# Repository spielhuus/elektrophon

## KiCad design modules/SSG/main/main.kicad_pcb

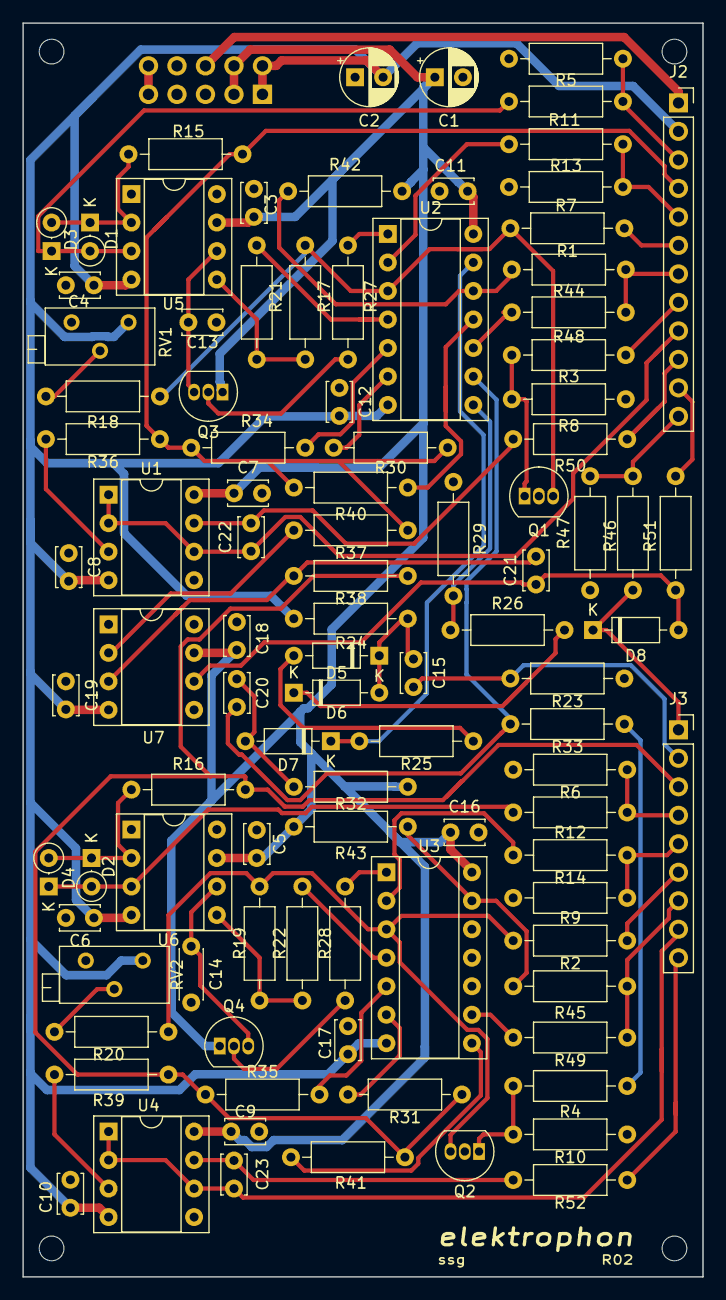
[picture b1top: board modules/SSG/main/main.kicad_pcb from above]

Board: 2 copper layers, 60.6 x 111.8 mm, 99 parts (1 on the bottom side), 70 nets.

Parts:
C1, C2: 10u; CP_Radial_D5.0mm_P2.50mm
C3, C4, C5, C6, C7, C8, C9, C10, C11, C12, C16, C17, C18, C19: 0.1u; C_Disc_D3.4mm_W2.1mm_P2.50mm
C13: 100n; C_Disc_D3.4mm_W2.1mm_P2.50mm
C14: 220n; C_Disc_D4.3mm_W1.9mm_P5.00mm
C15, C20: 1n; C_Disc_D3.4mm_W2.1mm_P2.50mm
C21: 100p; C_Disc_D3.4mm_W2.1mm_P2.50mm
C22, C23: 47p; C_Disc_D3.4mm_W2.1mm_P2.50mm
D1, D2, D3, D4: 1N4148; D_DO-35_SOD27_P2.54mm_Vertical_KathodeUp
D5, D6, D7, D8: 1N4148; D_DO-35_SOD27_P7.62mm_Horizontal
J1: IDC Header; IDC-Header_2x05_P2.54mm_Vertical
J2: Conn_01x12_Female; PinSocket_1x12_P2.54mm_Vertical
J3: Conn_01x09_Female; PinSocket_1x09_P2.54mm_Vertical
Q1, Q2: PN4250; TO-92_Inline
Q3, Q4: J201; TO-92_Inline
R1, R2, R13, R14: 2M7; R_Axial_DIN0207_L6.3mm_D2.5mm_P10.16mm_Horizontal
R3, R4, R5, R6, R11, R12, R15, R16, R24: 33k; R_Axial_DIN0207_L6.3mm_D2.5mm_P10.16mm_Horizontal
R7, R9, R23, R26: 100k; R_Axial_DIN0207_L6.3mm_D2.5mm_P10.16mm_Horizontal
R8, R10, R21, R22: 15k; R_Axial_DIN0207_L6.3mm_D2.5mm_P10.16mm_Horizontal
R17, R19: 82k; R_Axial_DIN0207_L6.3mm_D2.5mm_P10.16mm_Horizontal
R18, R20, R32: 1M5; R_Axial_DIN0207_L6.3mm_D2.5mm_P10.16mm_Horizontal
R25: 680k; R_Axial_DIN0207_L6.3mm_D2.5mm_P10.16mm_Horizontal
R27, R31: 820k; R_Axial_DIN0207_L6.3mm_D2.5mm_P10.16mm_Horizontal
R28: 1m; R_Axial_DIN0207_L6.3mm_D2.5mm_P10.16mm_Horizontal
R29: 4M7; R_Axial_DIN0207_L6.3mm_D2.5mm_P10.16mm_Horizontal
R30, R42, R43: 1M; R_Axial_DIN0207_L6.3mm_D2.5mm_P10.16mm_Horizontal
R33, R34, R35: 330; R_Axial_DIN0207_L6.3mm_D2.5mm_P10.16mm_Horizontal
R36, R37, R38, R39: 10k; R_Axial_DIN0207_L6.3mm_D2.5mm_P10.16mm_Horizontal
R40, R41: 470k; R_Axial_DIN0207_L6.3mm_D2.5mm_P10.16mm_Horizontal
R44, R45: 2M2; R_Axial_DIN0207_L6.3mm_D2.5mm_P10.16mm_Horizontal
R46, R47, R48, R49, R51: 3k3; R_Axial_DIN0207_L6.3mm_D2.5mm_P10.16mm_Horizontal
R50, R52: 100; R_Axial_DIN0207_L6.3mm_D2.5mm_P10.16mm_Horizontal
RV1, RV2: 25k; Potentiometer_Bourns_3296Z_Horizontal
U1, U4: TL072; DIP-8_W7.62mm_Socket
U2, U3: LM3900; DIP-14_W7.62mm_Socket
U5, U6: CA3080; DIP-8_W7.62mm_Socket
U7: LM741; DIP-8_W7.62mm_Socket

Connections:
+5V: J1.9, J1.10
+15V: C1.1, C3.1, C5.1, C7.1, C9.1, C11.1, C16.1, C18.1, J1.3, J1.4, Q3.1, Q4.1, R32.2, R42.2, R43.2, U1.8, U2.14, U3.14, U4.8, U5.7, U6.7, U7.7
-15V: C2.2, C4.2, C6.2, C8.2, C10.2, C12.2, C17.2, C19.2, J1.1, J1.2, J2.2, R24.1, RV1.1, RV2.1, U1.4, U2.7, U3.7, U4.4, U5.4, U6.4, U7.4
/HOLD: R4.2, R33.1
COUPLER_5V: J2.12, R46.1, R47.2
COUPLER_HOT: J2.11, R51.1
CYCLE_1: J2.7, R44.1, R48.1
CYCLE_2: J3.7, R45.1, R49.1
GND: C1.2, C2.1, C3.2, C4.1, C5.2, C6.1, C7.2, C8.1, C9.2, C10.1, C11.2, C12.1, C13.2, C14.2, C16.2, C17.1, C18.2, C19.1, J1.5, J1.6, J1.7, J1.8, J2.1, Q1.2, Q2.2, R5.1, R6.1, R7.1, R8.1, R9.1, R10.1, R23.1, R29.1, R47.1, RV1.3, RV2.3, U1.5, U4.5
HOLD_1: J2.8, R3.2
IN_1: J2.3, R5.2, R11.2
IN_2: J3.4, R6.2, R12.2
LED: D8.1, J3.1, R46.2
LED_1_a: C22.1, J2.9, U1.1, U1.2, U1.6
LED_1_b: J2.10, R50.1
LED_2_a: C23.1, J3.8, U4.1, U4.2, U4.6
LED_2_b: J3.9, R52.1
unnamed: C13.1, Q3.3, U5.6
unnamed: C14.1, Q4.3, U6.6
unnamed: C15.2, D5.1, D6.2, R24.2
unnamed: C20.1, R33.2, U2.9
unnamed: C20.2, D7.2, R32.1
unnamed: C21.1, D8.2, R51.2, U7.6
unnamed: C21.2, R38.1, U7.3
unnamed: C22.2, R50.2, U1.7
unnamed: C23.2, R52.2, U4.7
unnamed: D1.1, D3.2, R15.2, U5.2
unnamed: D1.2, D3.1, R11.1, U5.3
unnamed: D2.1, D4.2, R16.2, U6.2
unnamed: D2.2, D4.1, R12.1, U6.3
unnamed: D5.2, R25.2
unnamed: D6.1, R26.2
unnamed: D7.1, R25.1, U2.13
unnamed: Q1.1, R3.1, R8.2
unnamed: Q1.3, R1.1, R17.2, R18.2, U2.3
unnamed: Q2.1, R4.1, R10.2
unnamed: Q2.3, R2.1, R19.2, R20.2, U3.3
unnamed: Q3.2, R27.2
unnamed: Q4.2, R28.2
unnamed: R13.1, U2.2
unnamed: R14.1, U3.2
unnamed: R17.1, R21.1, U5.5
unnamed: R18.1, RV1.2
unnamed: R19.1, R22.1, U6.5
unnamed: R20.1, RV2.2
unnamed: R21.2, U2.4
unnamed: R22.2, U3.4
unnamed: R26.1, R29.2, U2.8
unnamed: R27.1, U2.1
unnamed: R28.1, U3.1
unnamed: R30.1, U2.6
unnamed: R31.1, U3.6
unnamed: R34.2, U2.5
unnamed: R35.2, U3.5
unnamed: R36.1, U1.3
unnamed: R37.1, U7.2
unnamed: R39.1, U4.3
unnamed: R40.1, U2.11
unnamed: R41.1, U3.8
unnamed: R42.1, R44.2, U2.12
unnamed: R43.1, R45.2, U3.13
unnamed: R48.2, U2.10
unnamed: R49.2, U3.9
OUT_1: J2.4, R15.1, R30.2, R34.1, R36.2, R37.2, R40.2
OUT_2: J3.3, R16.1, R31.2, R35.1, R38.2, R39.2, R41.2
RATE_1: J2.6, R1.2
RATE_2: J3.6, R2.2
SAMPLE_2: C15.1, J3.2, R23.2
VC_1: J2.5, R7.2, R13.2
VC_2: J3.5, R9.2, R14.2

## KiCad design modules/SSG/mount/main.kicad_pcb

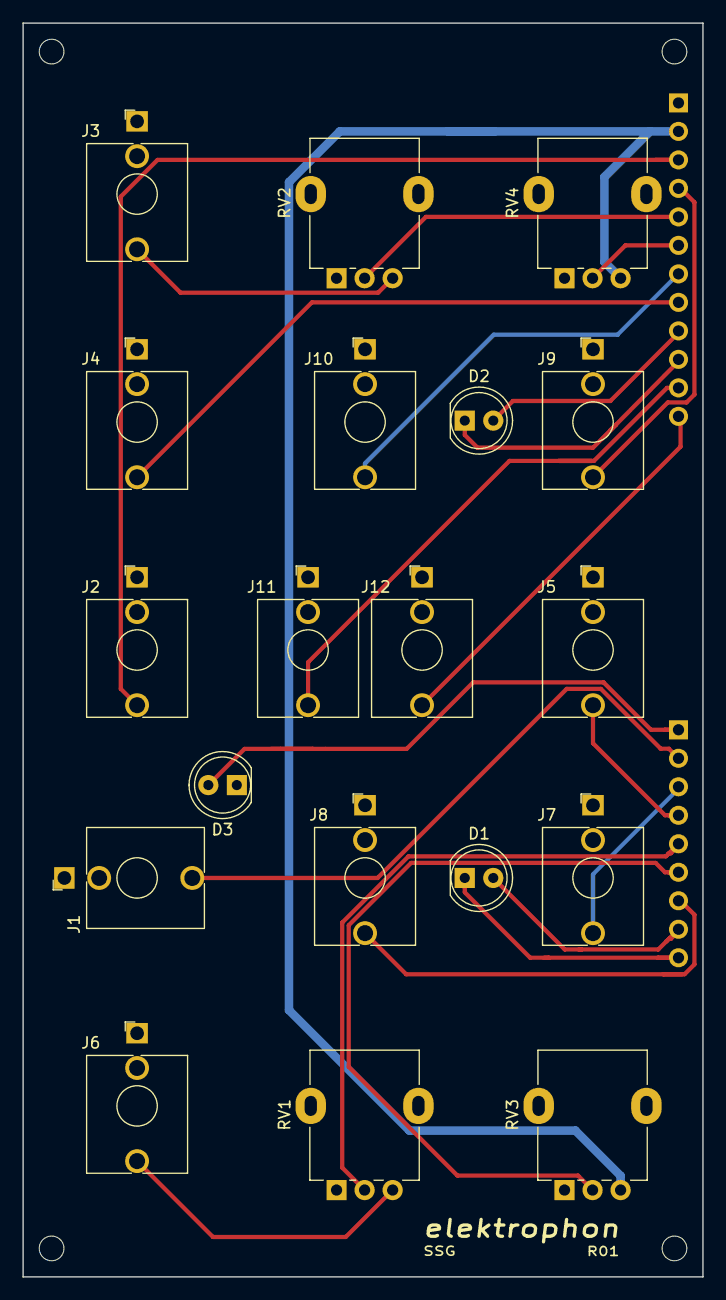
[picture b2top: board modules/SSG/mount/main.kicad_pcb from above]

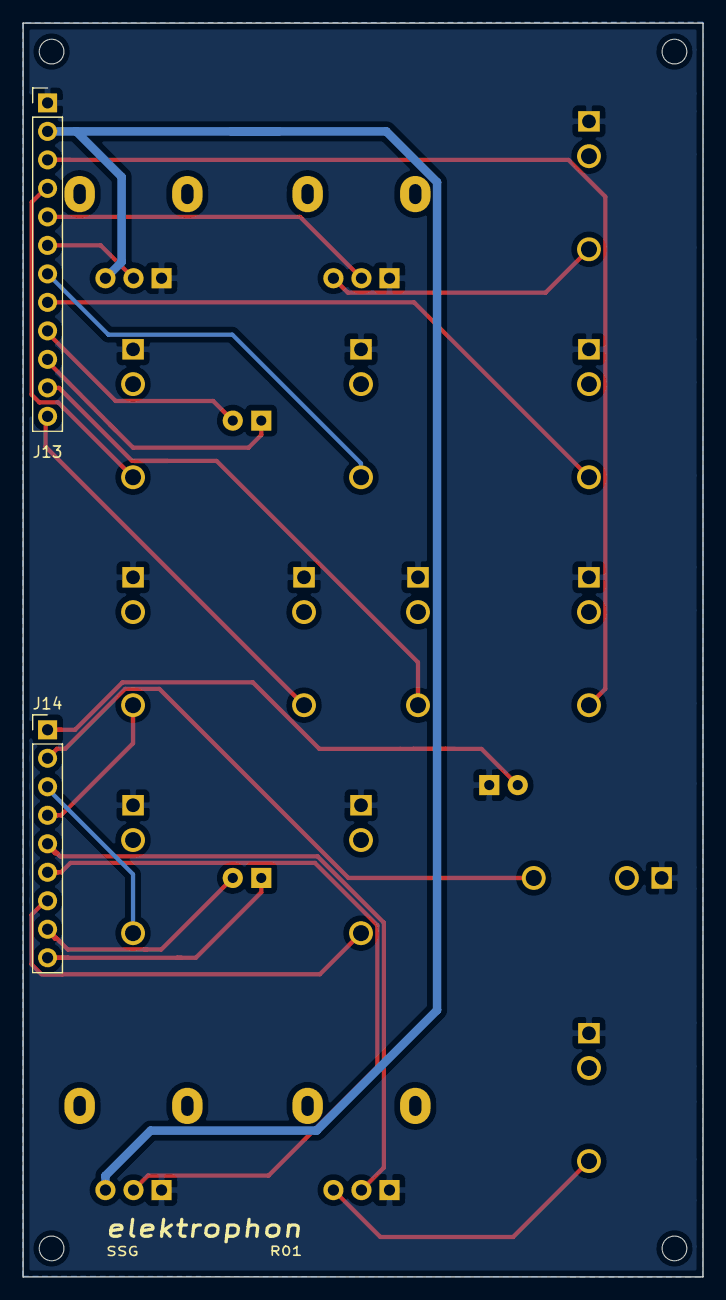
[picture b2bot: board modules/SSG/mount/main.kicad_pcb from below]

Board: 2 copper layers, 60.6 x 111.8 mm, 21 parts (2 on the bottom side), 23 nets.

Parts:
D1, D2: LED_Dual_2pin; LED_D5.0mm
D3: LED; LED_D5.0mm
J1: SAMPLE; Jack_3.5mm_WQP-PJ398SM_Vertical
J2, J5: IN; Jack_3.5mm_WQP-PJ398SM_Vertical
J3, J6: VC; Jack_3.5mm_WQP-PJ398SM_Vertical
J4: HOLD; Jack_3.5mm_WQP-PJ398SM_Vertical
J7, J9: OUT; Jack_3.5mm_WQP-PJ398SM_Vertical
J8, J10: CYCLE; Jack_3.5mm_WQP-PJ398SM_Vertical
J11: HOT; Jack_3.5mm_WQP-PJ398SM_Vertical
J12: 5V; Jack_3.5mm_WQP-PJ398SM_Vertical
J13: Conn_01x12_Male; PinHeader_1x12_P2.54mm_Vertical
J14: Conn_01x09_Male; PinHeader_1x09_P2.54mm_Vertical
RV1, RV2, RV3, RV4: 50k; Potentiometer_Alpha_RD901F-40-00D_Single_Vertical

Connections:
-15V: J13.2, RV3.3, RV4.3
COUPLER_5V: J12.T, J13.12
COUPLER_HOT: J11.T, J13.11
CYCLE_1: J10.T, J13.7
CYCLE_2: J8.T, J14.7
GND: D3.1, J1.S, J2.S, J3.S, J4.S, J5.S, J6.S, J7.S, J8.S, J9.S, J10.S, J11.S, J12.S, J13.1, RV1.1, RV2.1, RV3.1, RV4.1
HOLD_1: J4.T, J13.8
IN_1: J2.T, J13.3
IN_2: J5.T, J14.4
LED: D3.2, J14.1
LED_1_a: D2.2, J13.9
LED_1_b: D2.1, J13.10
LED_2_a: D1.2, J14.8
LED_2_b: D1.1, J14.9
unnamed: J3.T, RV2.3
unnamed: J6.T, RV1.3
OUT_1: J9.T, J13.4
OUT_2: J7.T, J14.3
RATE_1: J13.6, RV4.2
RATE_2: J14.6, RV3.2
SAMPLE_2: J1.T, J14.2
VC_1: J13.5, RV2.2
VC_2: J14.5, RV1.2

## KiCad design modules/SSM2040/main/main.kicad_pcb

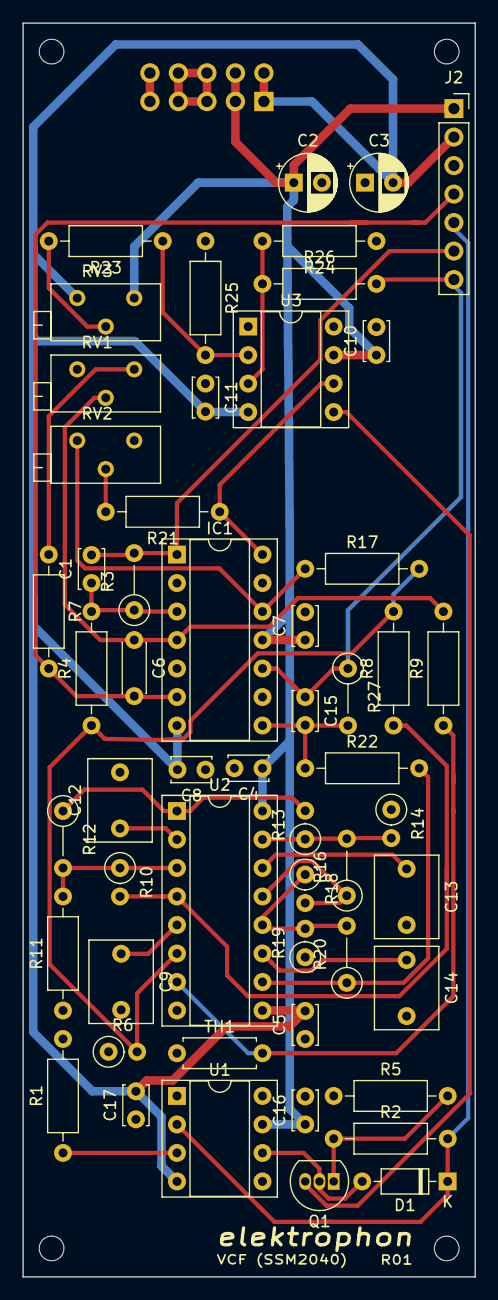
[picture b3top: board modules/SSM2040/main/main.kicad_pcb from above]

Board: 2 copper layers, 40.3 x 111.8 mm, 59 parts (1 on the bottom side), 35 nets.

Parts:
C1: 47p; C_Disc_D3.4mm_W2.1mm_P2.50mm
C2, C3: 10u; CP_Radial_D5.0mm_P2.50mm
C4, C5, C7, C8, C10, C11, C16, C17: 0.1u; C_Disc_D3.4mm_W2.1mm_P2.50mm
C6: 0.05u; C_Disc_D4.3mm_W1.9mm_P5.00mm
C9, C12, C13, C14: 0.01; C_Rect_L7.2mm_W5.5mm_P5.00mm_FKS2_FKP2_MKS2_MKP2
C15: 10p; C_Disc_D3.4mm_W2.1mm_P2.50mm
D1: 1N4148; D_DO-35_SOD27_P7.62mm_Horizontal
H1, H2, H3, H4: MountingHole; MountingHole_2.2mm_M2
IC1: RC4136; DIP-14_W7.62mm_Socket
J1: IDC Header; IDC-Header_2x05_P2.54mm_Vertical
J2: Conn_01x07_Female; PinSocket_1x07_P2.54mm_Vertical
Q1: 2N3906; TO-92_Inline
R1: 27k; R_Axial_DIN0207_L6.3mm_D2.5mm_P10.16mm_Horizontal
R2, R26: 100k; R_Axial_DIN0207_L6.3mm_D2.5mm_P10.16mm_Horizontal
R3, R12, R16, R20: 10k; R_Axial_DIN0207_L6.3mm_D2.5mm_P5.08mm_Vertical
R4, R8, R17, R22: 10k; R_Axial_DIN0207_L6.3mm_D2.5mm_P10.16mm_Horizontal
R5: 39k; R_Axial_DIN0207_L6.3mm_D2.5mm_P10.16mm_Horizontal
R6, R14, R19: 200; R_Axial_DIN0207_L6.3mm_D2.5mm_P2.54mm_Vertical
R7: 91k; R_Axial_DIN0207_L6.3mm_D2.5mm_P10.16mm_Horizontal
R9: 56k; R_Axial_DIN0207_L6.3mm_D2.5mm_P10.16mm_Horizontal
R10, R13, R18: 10k; R_Axial_DIN0207_L6.3mm_D2.5mm_P2.54mm_Vertical
R11, R24, R25: 200; R_Axial_DIN0207_L6.3mm_D2.5mm_P10.16mm_Horizontal
R21: 33k; R_Axial_DIN0207_L6.3mm_D2.5mm_P10.16mm_Horizontal
R23: 220k; R_Axial_DIN0207_L6.3mm_D2.5mm_P10.16mm_Horizontal
R27: 100k; R_Axial_DIN0207_L6.3mm_D2.5mm_P5.08mm_Vertical
RV1: 25k; Potentiometer_Bourns_3296Z_Horizontal
RV2: 10k; Potentiometer_Bourns_3296Z_Horizontal
RV3: 100k; Potentiometer_Bourns_3296Z_Horizontal
TH1: Thermistor 1k; R_Axial_DIN0207_L6.3mm_D2.5mm_P7.62mm_Horizontal
U1: LM741; DIP-8_W7.62mm_Socket
U2: SSM2040; DIP-16_W7.62mm_Socket
U3: CA3080; DIP-8_W7.62mm_Socket

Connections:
+5V: J1.9, J1.10
+15V: C2.1, C4.1, C7.1, C10.1, C16.1, IC1.11, J1.3, J1.4, J2.1, RV3.1, U1.7, U2.16, U3.7
-15V: C3.2, C5.2, C8.2, C11.2, C17.2, IC1.7, J1.1, J1.2, J2.2, RV3.3, U1.4, U2.9, U3.4
/BIAS: Q1.3, U3.5
/CNTL: R9.1, TH1.2, U2.7
/IN: C1.2, IC1.1, J2.6, R3.2
/OUT: C15.1, IC1.10, J2.7, R26.2, R27.1
/RES: D1.1, J2.5, R2.2, U1.2
/VC: C6.2, IC1.6, J2.4, R7.2
GND: C2.2, C3.1, C4.2, C5.1, C7.2, C8.1, C9.2, C10.2, C11.1, C12.2, C13.2, C14.2, C16.2, C17.1, IC1.2, IC1.5, IC1.9, IC1.13, J1.5, J1.6, J1.7, J1.8, J2.3, R1.2, R5.1, R6.1, R11.1, R14.1, R19.1, R24.1, R25.1, TH1.1, U2.8
unnamed: C1.1, IC1.3, R3.1, R4.2
unnamed: C6.1, IC1.4, R9.2, RV1.2
unnamed: C9.1, U2.5
unnamed: C12.1, U2.2
unnamed: C13.1, U2.14
unnamed: C14.1, U2.11
unnamed: C15.2, IC1.8, R22.1, R27.2
unnamed: D1.2, Q1.2, U1.6
unnamed: IC1.12, R17.1, RV2.3
unnamed: IC1.14, R21.1, U3.6
unnamed: Q1.1, R2.1, R5.2
unnamed: R1.1, U1.3
unnamed: R7.1, RV1.1
unnamed: R10.1, R11.2, R12.2, U2.3
unnamed: R8.1, R10.2, U2.4
unnamed: R12.1, R13.2, U2.1
unnamed: R13.1, R14.2, R16.2, U2.15
unnamed: R16.1, R18.2, U2.13
unnamed: R4.1, R6.2, R8.2, R17.2, U2.6
unnamed: R18.1, R19.2, R20.2, U2.12
unnamed: R20.1, R22.2, U2.10
unnamed: R21.2, RV2.2
unnamed: R23.1, R25.2, U3.2
unnamed: R23.2, RV3.2
unnamed: R24.2, R26.1, U3.3

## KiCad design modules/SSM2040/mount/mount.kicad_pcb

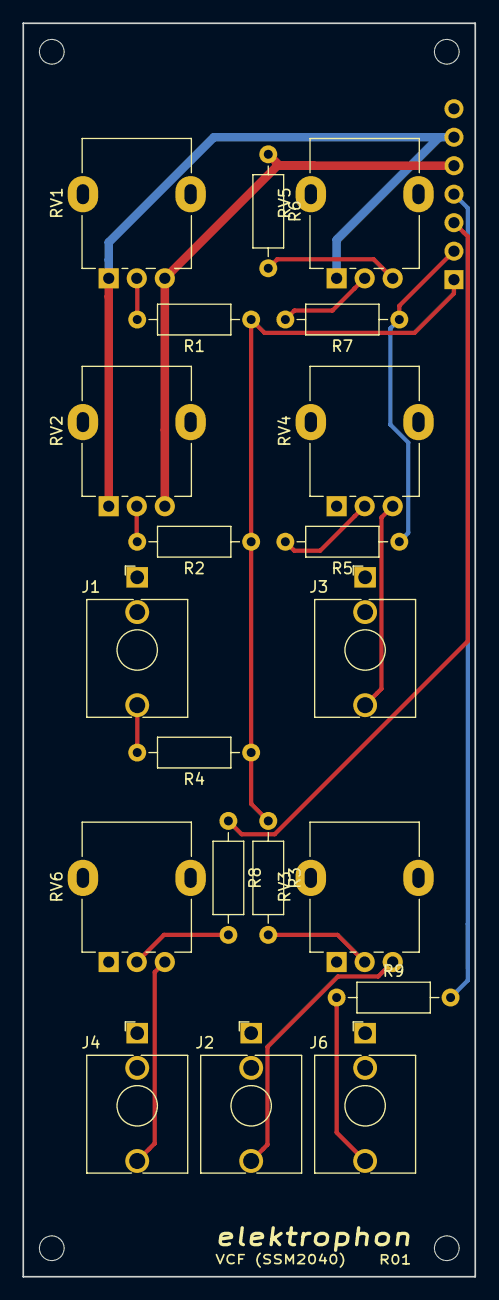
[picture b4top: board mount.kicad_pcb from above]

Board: 2 copper layers, 40.3 x 111.8 mm, 25 parts (1 on the bottom side), 19 nets.

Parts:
H1, H2, H3, H4: MountingHole; MountingHole_2.2mm_M2
J1: 1V/OCT; Jack_3.5mm_WQP-PJ398SM_Vertical
J2: ENVELOPE; Jack_3.5mm_WQP-PJ398SM_Vertical
J3: RESONANCE; Jack_3.5mm_WQP-PJ398SM_Vertical
J4: INPUT; Jack_3.5mm_WQP-PJ398SM_Vertical
J5: Conn_01x07_Male; PinHeader_1x07_P2.54mm_Vertical
J6: OUT; Jack_3.5mm_WQP-PJ398SM_Vertical
R1: 150k; R_Axial_DIN0207_L6.3mm_D2.5mm_P10.16mm_Horizontal
R2: 2M2; R_Axial_DIN0207_L6.3mm_D2.5mm_P10.16mm_Horizontal
R3: 33k; R_Axial_DIN0207_L6.3mm_D2.5mm_P10.16mm_Horizontal
R4, R5, R8: 100k; R_Axial_DIN0207_L6.3mm_D2.5mm_P10.16mm_Horizontal
R6: 18k; R_Axial_DIN0207_L6.3mm_D2.5mm_P10.16mm_Horizontal
R7: 47k; R_Axial_DIN0207_L6.3mm_D2.5mm_P10.16mm_Horizontal
R9: 1k; R_Axial_DIN0207_L6.3mm_D2.5mm_P10.16mm_Horizontal
RV1, RV2, RV3, RV4, RV5, RV6: 100k; Potentiometer_Alpha_RD901F-40-00D_Single_Vertical

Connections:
+15V: J5.5, R6.1, RV1.3, RV2.3
-15V: J5.6, RV1.1, RV2.1, RV5.1
/IN: J5.3, R8.1
/OUT: J5.4, R9.2
/RES: J5.2, R5.1, R7.1
/VC: J5.1, R1.1, R2.1, R3.1, R4.1
GND: J1.S, J2.S, J3.S, J4.S, J5.7, J6.S, RV3.1, RV4.1, RV6.1
unnamed: J1.T, R4.2
unnamed: J2.T, RV3.3
unnamed: J3.T, RV4.3
unnamed: J4.T, RV6.3
unnamed: J6.T, R9.1
unnamed: R1.2, RV1.2
unnamed: R2.2, RV2.2
unnamed: R3.2, RV3.2
unnamed: R5.2, RV4.2
unnamed: R6.2, RV5.3
unnamed: R7.2, RV5.2
unnamed: R8.2, RV6.2

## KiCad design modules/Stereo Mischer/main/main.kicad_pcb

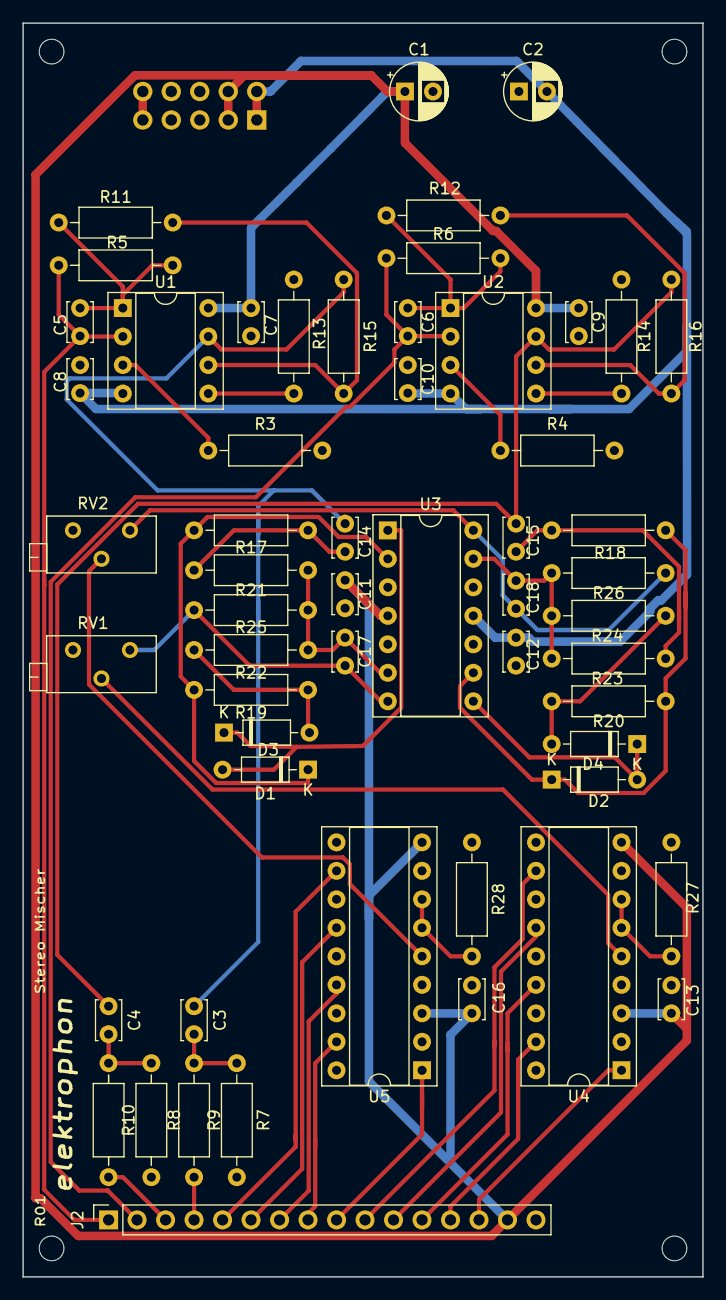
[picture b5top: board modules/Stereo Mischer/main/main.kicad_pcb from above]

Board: 2 copper layers, 60.6 x 111.8 mm, 57 parts (1 on the bottom side), 46 nets.

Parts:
C1, C2: 10u; CP_Radial_D5.0mm_P2.50mm
C3, C4: 4u7; C_Disc_D3.4mm_W2.1mm_P2.50mm
C5, C6: 47p; C_Disc_D3.4mm_W2.1mm_P2.50mm
C7, C8, C9, C10, C11, C12, C13, C16, C17, C18: 0.1u; C_Disc_D3.4mm_W2.1mm_P2.50mm
C14, C15: 0.47u; C_Disc_D3.4mm_W2.1mm_P2.50mm
D1, D2, D3, D4: 1N4148; D_DO-35_SOD27_P7.62mm_Horizontal
J1: IDC Header; IDC-Header_2x05_P2.54mm_Vertical
J2: Conn_01x16_Female; PinSocket_1x16_P2.54mm_Vertical
R3, R4, R7, R8, R13, R14: 5k; R_Axial_DIN0207_L6.3mm_D2.5mm_P10.16mm_Horizontal
R5, R6, R11, R12, R15, R16: 10k; R_Axial_DIN0207_L6.3mm_D2.5mm_P10.16mm_Horizontal
R9, R10: 1k; R_Axial_DIN0207_L6.3mm_D2.5mm_P10.16mm_Horizontal
R17, R18, R19, R20, R22, R24: 47k; R_Axial_DIN0207_L6.3mm_D2.5mm_P10.16mm_Horizontal
R21, R23, R25, R26: 100k; R_Axial_DIN0207_L6.3mm_D2.5mm_P10.16mm_Horizontal
R27, R28: 3k3; R_Axial_DIN0207_L6.3mm_D2.5mm_P10.16mm_Horizontal
RV1, RV2: 10k; Potentiometer_Bourns_3296Z_Horizontal
U1, U2: NE5532; DIP-8_W7.62mm_Socket
U3: TL074; DIP-14_W7.62mm_Socket
U4, U5: lm3916; DIP-18_W7.62mm_Socket

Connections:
+5V: J1.9, J1.10
+15V: C1.1, C7.1, C9.1, C11.1, C13.1, C16.1, J1.3, J1.4, J2.15, U1.8, U2.8, U3.4, U4.3, U4.9, U5.3, U5.9
-15V: C2.2, C8.2, C10.2, C12.2, J1.1, J1.2, U1.4, U2.4, U3.11
/LED_L_1: J2.14, U4.1
/LED_L_2: J2.13, U4.17
/LED_L_3: J2.12, U4.15
/LED_L_4: J2.11, U4.13
/LED_L_5: J2.10, U4.11
/LED_R_1: J2.9, U5.1
/LED_R_2: J2.8, U5.17
/LED_R_3: J2.7, U5.15
/LED_R_4: J2.6, U5.13
/LED_R_5: J2.5, U5.11
/LEFT: C5.2, J2.1, R5.2, U1.2
/LEFT_OUT: C3.1, C14.2, R15.1, U1.7
/RIGHT: C6.2, J2.2, R6.2, U2.2
/RIGHT_OUT: C4.1, C15.2, R16.1, U2.7
/STEREO_L: J2.4, R9.1
/STEREO_R: J2.3, R10.1
GND: C1.2, C2.1, C7.2, C8.1, C9.2, C10.1, C11.2, C12.1, C13.2, C16.2, J1.5, J1.6, J1.7, J1.8, J2.16, R3.2, R4.2, R7.2, R8.2, R13.2, R14.2, R27.1, R28.1, RV1.3, RV2.3, U3.3, U3.5, U3.10, U3.12, U4.2, U4.4, U4.8, U5.2, U5.4, U5.8
unnamed: C3.2, R7.1, R9.2
unnamed: C4.2, R8.1, R10.2
unnamed: C5.1, R5.1, R11.2, U1.1
unnamed: C6.1, R6.1, R12.2, U2.1
unnamed: C14.1, R17.2, R21.2
unnamed: C15.1, R18.2, R23.2
unnamed: C17.1, R25.1, RV1.1, U3.7
unnamed: C17.2, R21.1, R22.1, R25.2, U3.6
unnamed: C18.1, R26.1, RV2.1, U3.14
unnamed: C18.2, R23.1, R24.1, R26.2, U3.13
unnamed: D1.1, R17.1, R19.2, U3.2
unnamed: D1.2, D3.1, U3.1
unnamed: D2.1, R18.1, R20.2, U3.9
unnamed: D2.2, D4.1, U3.8
unnamed: D3.2, R19.1, R22.2
unnamed: D4.2, R20.1, R24.2
unnamed: R3.1, U1.3
unnamed: R4.1, U2.3
unnamed: R11.1, R15.2, U1.6
unnamed: R12.1, R16.2, U2.6
unnamed: R13.1, U1.5
unnamed: R14.1, U2.5
unnamed: R27.2, U4.6, U4.7
unnamed: R28.2, U5.6, U5.7
unnamed: RV1.2, U4.5
unnamed: RV2.2, U5.5

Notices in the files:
modules/SSG/main/main.kicad_pcb:
License CC BY 4.0 - Attribution 4.0 International
